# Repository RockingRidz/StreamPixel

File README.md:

# StreamPixel

StreamPixel is Ridith Shetty's three-panel RGB display project, using an ESP32 development board, perfboard, two 5V logic buffers and a MAX9814 microphone. Three nominal 320 × 160 mm P10 panels form a 960 × 160 mm display with 96 × 16 pixels. Local phone/browser controls provide scrolling text, colour animation/test and relative microphone activity.

**This is a design and prototype handoff, not a claim of assembled, tested hardware. No custom PCB order is required.**

The reference-layout image shows placeholder panel thickness and supply dimensions. It is not a photo or a physical fit test.

## Files to use

- [CAD](CAD/): genuine editable FreeCAD source, STEP geometry, native Onshape FeatureScript source and the manufacturing handoff. The source is `.FCStd` plus STEP; these are not renamed Fusion `.f3d` files.
- [CNC parts](CAD/CNC/): **one whole frame, one whole backplate, six panel retainers, four wall spacers and two hanger pads**. Use the 3D STEP files for milling; DXFs describe only their indicated flat profiles.
- [3D-printed holders](CAD/3D_PRINTED/): **controller tray and two supply-holder halves only**. Print one of each STL. The supply holder is for the power supply, not a battery.
- [Perfboard schematic](PCB/StreamPixel-perfboard.kicad_sch), [KiCad project](PCB/StreamPixel-perfboard.kicad_pro) and [PDF](PCB/StreamPixel-perfboard.pdf). Keep the adjacent symbol library and `sym-lib-table` with the project. The `PCB` folder contains wiring documentation, not a PCB manufacturing order.
- [Firmware](FIRMWARE/README.md): ESP32 source, setup instructions and successful compile log. Actual display/microphone operation remains untested.
- [BOM with recorded prices and vendor links](BOM.csv).
- [Half Life journal](JOURNAL.md), mirrored from the project platform.

Native Onshape studios: [CNC frame, backplate and fittings](https://cad.onshape.com/documents/ff33f56b02d9867b20260f9d/w/d771c62f16da9b74f071b096/e/97cd61c99cbb00f7ac08fe59) and [3D-printed holders only](https://cad.onshape.com/documents/ff33f56b02d9867b20260f9d/w/d771c62f16da9b74f071b096/e/aeadc6d027d2d7d05235b7d8).

## Mechanical handoff

The whole frame is **990 × 190 × 60 mm**, with a **958 × 158 mm** front aperture and **962 × 162 mm** locating pocket. The rear plate is **990 × 190 × 3 mm**. Spacers extend the total front-to-wall depth to **78 mm**. StreamPixel and Ridith Shetty are recessed in the front border.

The deep frame is a **3D CNC milling job**, not a flat-sheet DXF cut. The shop must review stock, cutter access, internal corners, nut pockets, workholding, setups, material suitability and cost. No machine-specific CAM or G-code is supplied. Screws, nuts and wall anchors are purchased hardware, not CNC-cut acrylic parts.

Panel body thickness remains a **15 mm placeholder**; the supply reference remains an **unverified 220 × 60 × 25 mm envelope**. Actual connector/terminal space, gland grip, panel tolerances, screw reach, wall loads and temperature need verification before manufacture. A CAD overlap check cannot establish physical fit or structural capacity.

Hardware plan: **22 M3x10, four M3x25 and four M3x16 bolts; 30 M3 nuts**, plus suitable washers and wall anchors. Check actual fasteners and acrylic clamping before ordering.

## Wiring and software

Follow [the GPIO wiring guide](PCB/WIRING.md). The schematic uses logical printed labels for the development board and microphone; it does not guess their physical header positions. HCT buffer and proposed panel-connector pin numbers are shown explicitly. Three separately protected branches feed the panels, with a separate controller branch and common ground. MAX9814 uses 3.3V and GPIO34 (ADC1).

The active schematic passed KiCad ERC with **0 errors and 0 warnings**; its exported connectivity was checked against the selected GPIO mapping. Firmware compiled for **esp32:esp32:esp32**, using ESP32 core **3.3.11**, HUB75 library **3.0.14**, Adafruit GFX **1.12.6** and BusIO **1.17.4**. The build uses 963,684 bytes of flash and 48,672 bytes of global RAM. These are computer checks, not hardware test results.

Panel output is disabled by default until the actual scan ratio, driver, connector and row mapping are verified and configured. The normal HUB75 geometry is not an unidentified 1/4-scan P10 remap. First test one panel at low brightness, then configure the three-panel chain. Spotify integration is not implemented.

This is a plug-in 5V-supply build. Its holder is not a mains-rated enclosure. Suitable terminal guarding, earthing, strain relief and protected installation still need to be provided for the actual supply.

## Budget and work still required

Budget: **INR 6,445**. Carts checked on 1 November 2026: Koshi **INR 2,499**, Quartz **INR 1,526**, and Industrybuying **INR 578**, including its displayed INR 298 delivery. Total **INR 4,603**, leaving **INR 1,842** before remaining delivery and manufacturing. Quartz includes the MAX9814 microphone, 2m each of red/black power wire, 24 M3x10 bolts, four M3x25 bolts, four M3x15 bolts, 32 nuts, 24 washers and cable ties. The panel listing includes a power cable and FRC/data cable per module. Prices and availability remain subject to checkout; nothing has been purchased.

Still unquoted: the whole CNC frame and other CNC parts, three printed holder pieces, wall anchors, final supply-terminal protection/installation, any routing-dependent extra terminals/wires and remaining delivery. Tools are outside the parts carts. The final build is **not confirmed within INR 6,445**; obtain the CNC quote before ordering. The four M3x15 cart bolts are substitutes for the nominal M3x16 hanger-pad bolts: check the physical washer/plate/pad stack and full nut engagement before fitting. The 8mm-OD washers must not be inserted in the 7mm wall-foot head recesses.

Before making or demonstrating it:

1. Obtain the actual panel and supply measurements and update the model where needed.
2. Have the CNC shop approve machining details and quote the complete job; get a print quote for the holders.
3. Test fastener/joint fit and verify the mounting arrangement with the actual weight and wall.
4. Check unpowered continuity, power polarity, protection and actual module/panel pinouts.
5. Configure and test one panel, then three; measure current and enclosed temperatures.
6. Record real assembled photos and an honest working/failure demo. No physical result or manufacturing approval is claimed here.

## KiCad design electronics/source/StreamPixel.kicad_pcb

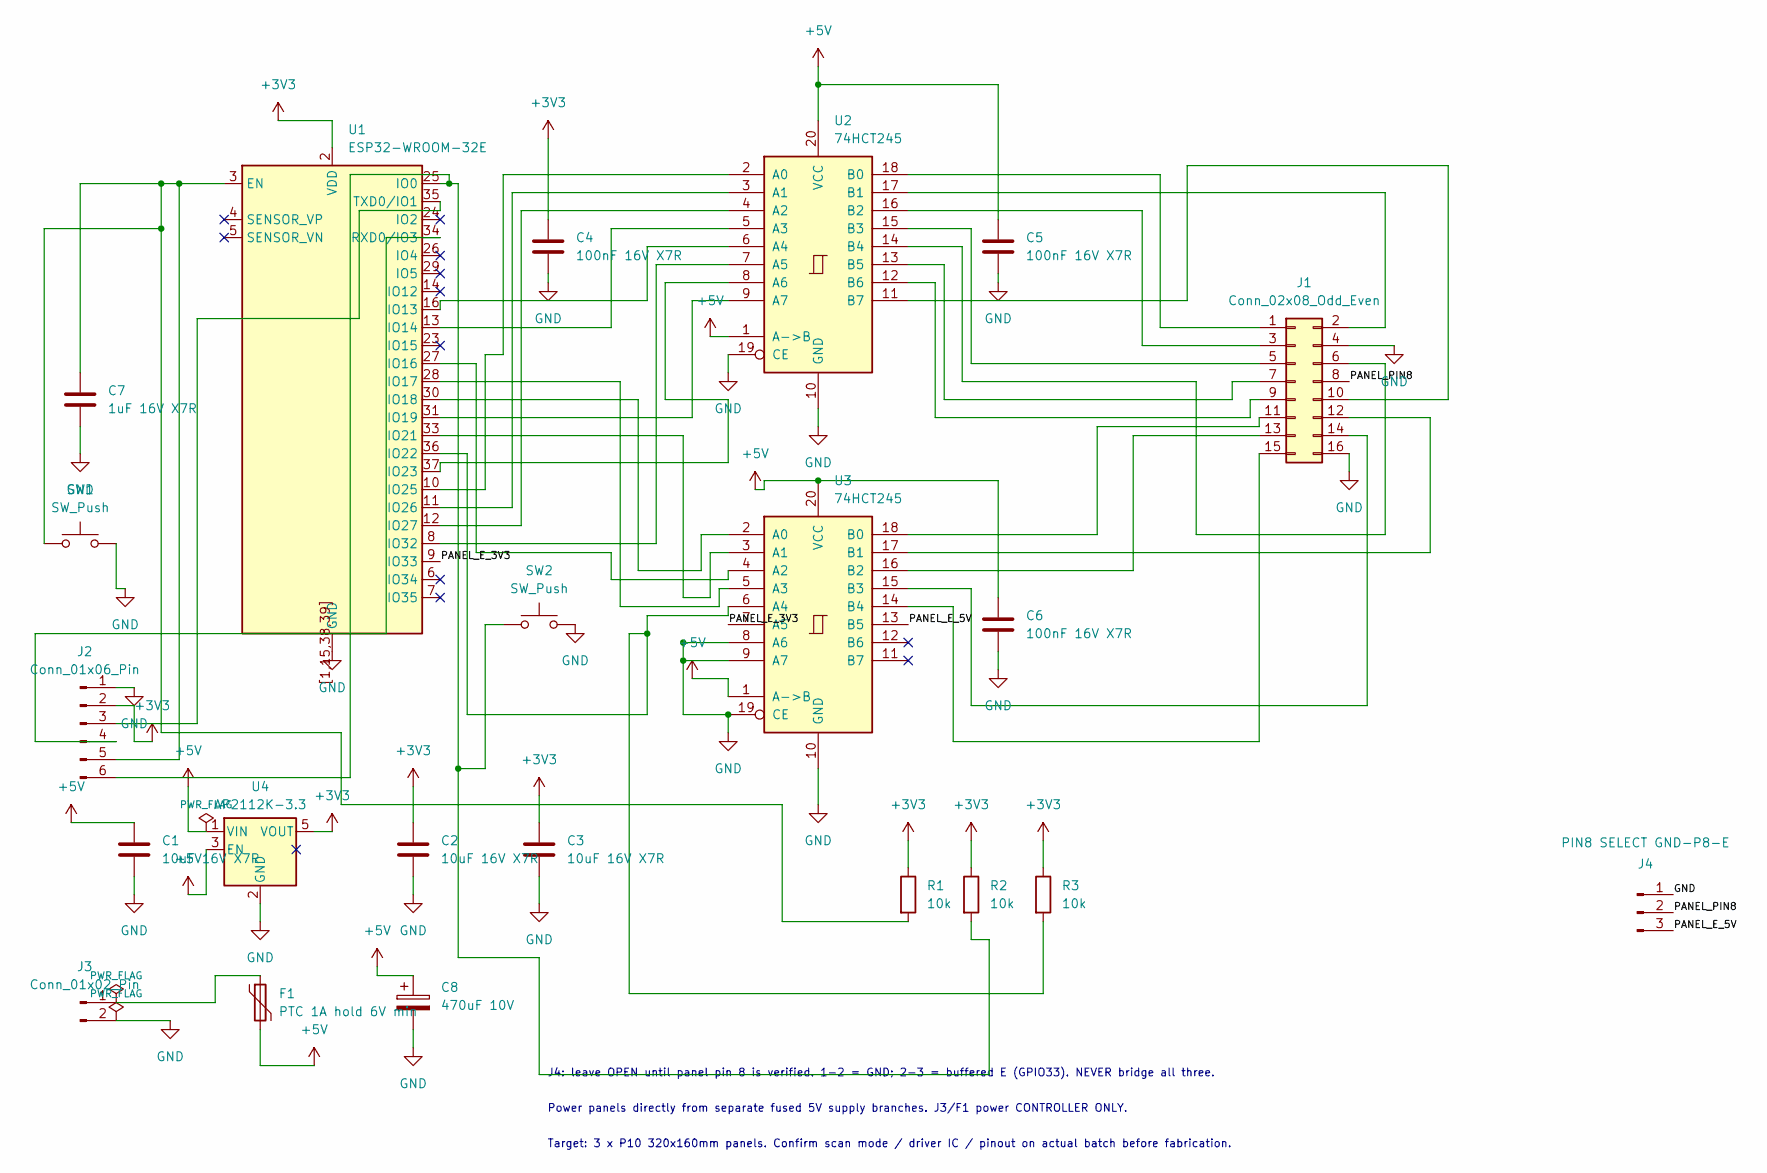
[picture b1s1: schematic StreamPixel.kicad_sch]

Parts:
C1, C2, C3: 10uF 16V X7R; C_0805_2012Metric
C4, C5, C6: 100nF 16V X7R; C_0805_2012Metric
C7: 1uF 16V X7R; C_0805_2012Metric
C8: 470uF 10V; CP_Radial_D8.0mm_P3.50mm
F1: PTC 1A hold 6V min; Fuse_1206_3216Metric
J1: Conn_02x08_Odd_Even; IDC-Header_2x08_P2.54mm_Vertical
J2: Conn_01x06_Pin; PinHeader_1x06_P2.54mm_Vertical
J3: Conn_01x02_Pin; TerminalBlock_Phoenix_MKDS-1,5-2-5.08_1x02_P5.08mm_Horizont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
J4: PIN8 SELECT GND-P8-E; PinHeader_1x03_P2.54mm_Vertical
R1, R2, R3: 10k; R_0805_2012Metric
SW1, SW2: SW_Push; SW_PUSH_6mm
U1: ESP32-WROOM-32E
U2, U3: 74HCT245; DIP-20_W7.62mm
U4: AP2112K-3.3; SOT-23-5

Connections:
+3V3: C2.1, C3.1, C4.1, J2.2, R1.1, R2.1, R3.1, U1.2 (VDD), U4.5 (VOUT)
+5V: C1.1, C5.1, C6.1, C8.1, F1.2, U2.1 (A->B), U2.20 (VCC), U3.1 (A->B), U3.20 (VCC), U4.1 (VIN), U4.3 (EN)
/PANEL_E_3V3: U1.9 (IO33), U3.7 (A5)
/PANEL_E_5V: J4.3, U3.13 (B5)
/PANEL_PIN8: J1.8, J4.2
GND: C1.2, C2.2, C3.2, C4.2, C5.2, C6.2, C7.2, C8.2, J1.4, J1.16, J2.1, J3.2, J4.1, SW1.2, SW2.2, U1.1, U1.15, U1.38, U1.39, U1.[1,15,38,39] (GND), U2.10 (GND), U2.19 (CE), U3.8 (A6), U3.9 (A7), U3.10 (GND), U3.19 (CE), U4.2 (GND)
unnamed: J1.1, U2.18 (B0)
unnamed: J1.2, U2.17 (B1)
unnamed: J1.3, U2.16 (B2)
unnamed: J1.5, U2.15 (B3)
unnamed: J1.6, U2.14 (B4)
unnamed: J1.7, U2.13 (B5)
unnamed: J1.9, U2.12 (B6)
unnamed: J1.10, U2.11 (B7)
unnamed: J1.11, U3.18 (B0)
unnamed: J1.12, U3.17 (B1)
unnamed: J1.13, U3.16 (B2)
unnamed: J1.14, U3.15 (B3)
unnamed: J1.15, U3.14 (B4)
unnamed: J2.3, U1.35 (TXD0/IO1)
unnamed: J2.4, U1.34 (RXD0/IO3)
unnamed: C7.1, J2.5, R1.2, SW1.1, U1.3 (EN)
unnamed: J2.6, R2.2, SW2.1, U1.25 (IO0)
unnamed: F1.1, J3.1
unnamed: U1.16 (IO13), U2.6 (A4)
unnamed: U1.13 (IO14), U2.5 (A3)
unnamed: U1.27 (IO16), U3.4 (A2)
unnamed: U1.28 (IO17), U3.5 (A3)
unnamed: U1.30 (IO18), U3.2 (A0)
unnamed: U1.31 (IO19), U2.9 (A7)
unnamed: U1.33 (IO21), U3.3 (A1)
unnamed: R3.2, U1.36 (IO22), U3.6 (A4)
unnamed: U1.37 (IO23), U2.8 (A6)
unnamed: U1.10 (IO25), U2.2 (A0)
unnamed: U1.11 (IO26), U2.3 (A1)
unnamed: U1.12 (IO27), U2.4 (A2)
unnamed: U1.8 (IO32), U2.7 (A5)

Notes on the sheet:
J4: leave OPEN until panel pin 8 is verified. 1-2 = GND; 2-3 = buffered E (GPIO33). NEVER bridge all three.
Power panels directly from separate fused 5V supply branches. J3/F1 power CONTROLLER ONLY.
Target: 3 x P10 320x160mm panels. Confirm scan mode / driver IC / pinout on actual batch before fabrication.

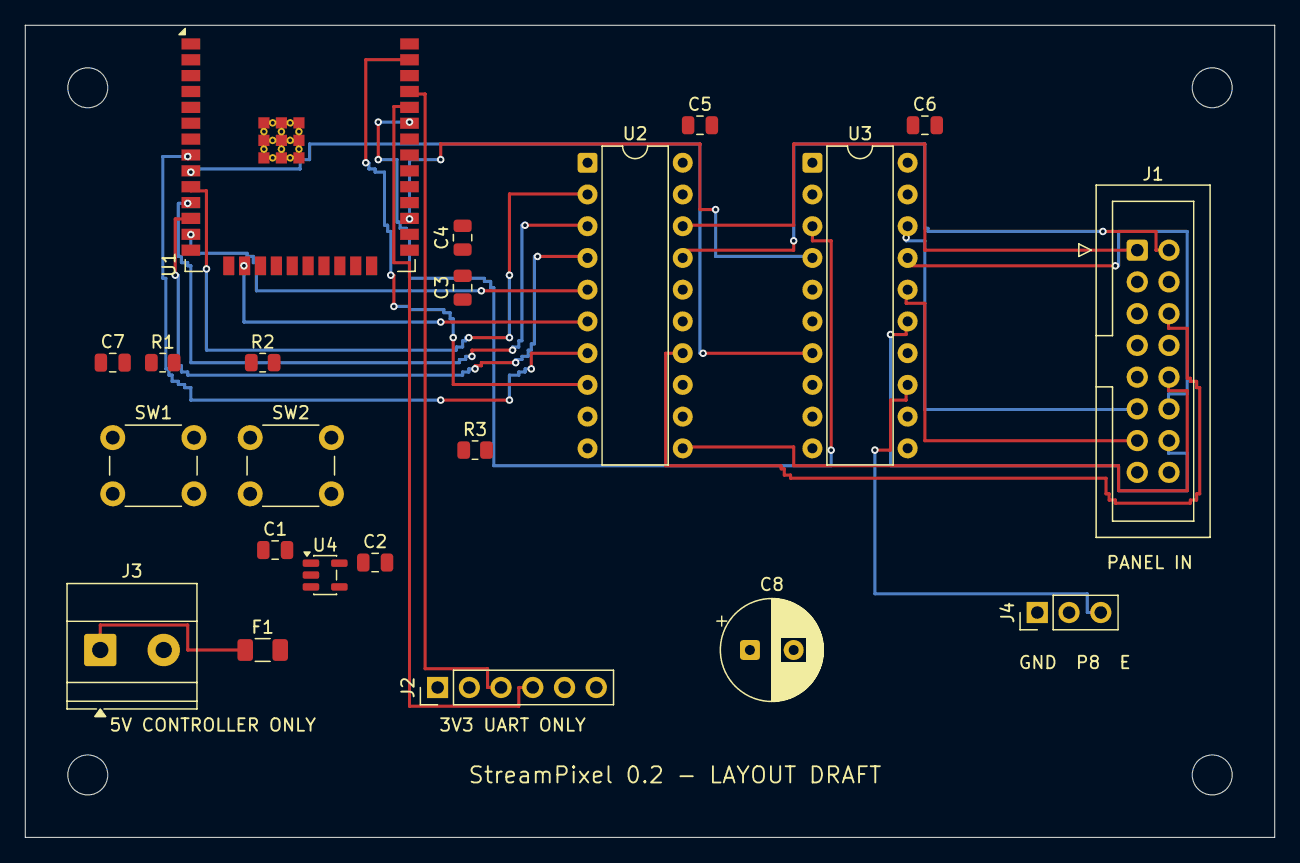
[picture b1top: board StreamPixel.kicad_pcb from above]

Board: 2 copper layers, 100.0 x 65.0 mm, 26 parts (0 on the bottom side), 37 nets.

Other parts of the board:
H1, H2, H3, H4: M3; MountingHole_3.2mm_M3
